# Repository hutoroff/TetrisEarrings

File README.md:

# ✨ TetrisEarrings

Earrings built on a 6×10 LED matrix with nine mesmerizing animated modes — from ping-pong and Tetris with an autonomous bot to fire, a starry sky, and rain on glass.

## About

A tiny STM32 board hidden inside the earring drives a matrix of 60 addressable RGB LEDs (6 columns × 10 rows). A single button switches modes manually, or they cycle on their own every 45 seconds. The device runs on a battery and can power itself off — either on a long button press or when the battery runs low — with a short farewell animation.

## Features

- 🎮 **9 modes** — from classic games to generative visual effects
- 🧠 **Tetris with a "smart" bot** — pieces don't just fall randomly: before each drop the bot tries every rotation and column and picks the placement using a heuristic (fewest holes, lowest height and bumpiness, most cleared lines)
- 🐍 **Snake with an autonomous bot** — finds its own path to the food and never runs into itself
- 🎨 **Sub-pixel smoothing** — the ping-pong balls move smoothly instead of jumping from LED to LED
- 🔋 **Smart power management** — continuous battery voltage monitoring and automatic shutdown on low battery
- 📺 **Power-off animation** — the screen "collapses" into a dot and fades out, like an old CRT TV
- 🧩 **Everything in 6 KB of RAM** — all modes share the same memory region (a union) instead of each mode keeping its own data

## Modes

| # | Mode | Description |
|---|---|---|
| 0 | Ping-Pong | Three balls fly around and bounce off each other, changing color on impact |
| 1 | Tetris | Autonomous game with a bot that deliberately chooses where to place each piece |
| 2 | Snake | Autonomous game; the bot steers the snake to the food by itself |
| 3 | Heart | A smoothly pulsing heart |
| 4 | Fire | Procedural simulation of a living flame with sparks |
| 5 | Matrix | Falling green "digital rain" in the style of *The Matrix* |
| 6 | Starry Sky | Sparse twinkling stars of different hues that slowly fade out |
| 7 | Rainbow | A shimmering diagonal rainbow wave |
| 8 | Rain on Glass | Drops trickle down and burst into splashes when they hit the bottom |

Short button press — next mode; hold for about a second — power off (with animation). With no presses, modes cycle automatically every 45 seconds.

## Hardware

| Parameter | Value |
|---|---|
| Microcontroller | STM32F070F6Px (Cortex-M0, 48 MHz, 32 KB Flash, 6 KB RAM) |
| Matrix | 6×10 (60 pcs) addressable RGB LEDs, WS2812-compatible protocol |
| Matrix data line | PA9 (TIM1_CH2 + DMA, per-bit PWM signal encoding) |
| Button | PA7 |
| Power control | PA6 (board power self-latch / shutdown) |
| Battery monitoring | PA1 (ADC1_IN1), auto-shutdown on low battery |
| Development environment | STM32CubeIDE 1.17.0, GNU Arm Embedded Toolchain 12.3.rel1 |

The matrix LEDs are wired in a "serpentine" layout: even rows run in one direction, odd rows in the other (see `GetLEDIndex()` in [ledMatrix.c](Core/Src/ledMatrix.c)).

### Power

1S Li-Po → P-MOSFET soft latch (button turns it on, PA6 holds it, PA6 low = off) → switched rail `VSW`. The LEDs run straight from `VSW` (3.5–4.2 V); the MCU gets 3.3 V from an LDO. Battery voltage is sensed on PA1 through a 62k/100k divider, so the firmware's 2700-count threshold means a **3.52 V** cutoff. Charging: MCP73831 at ~150 mA from two dock pads (the printed stand). Average draw ≈ 55–60 mA (mostly WS2812 idle current), so a 300 mAh 602030 cell gives ≈ 4.5 h.

### Components

| Qty | Ref | Part | Package | Note |
|---|---|---|---|---|
| 1 | U1 | STM32F070F6P6 | TSSOP-20 | MCU |
| 60 | LED1–LED60 | WS2812B-2020 | 2020 PLCC-4 | 6×10 matrix |
| 1 | U2 | MCP73831T-2ACI/OT | SOT-23-5 | Li-Po charger 4.2 V |
| 1 | U3 | ME6211C33M5G | SOT-23 | 3.3 V LDO |
| 1 | Q1 | AO3401A | SOT-23 | P-MOSFET power switch |
| 1 | Q2 | 2N7002 | SOT-23 | Latch driver |
| 2 | D1, D2 | BAT54W | SOD-323 | Latch OR diodes |
| 1 | D3 | LED red | 0603 | Charge indicator |
| 1 | Y1 | 8 MHz crystal | 3225 | HSE |
| 1 | SW1 | Tactile switch | SMD | Mode / power button |
| 1 | BT1 | Li-Po 1S 602030 300 mAh | 2 pads | With PCM; 602535 400 mAh for more runtime |
| — | J1 | TC2030-IDC-NL footprint | Tag-Connect pads | SWD; bare copper, nothing to buy |
| — | J2 | Dock contacts | 2 pads | 5 V charging; bare copper, nothing to buy |
| 5 | R1, R2, R3, R5, R8 | 100k | 0402 | Pull-ups/downs, dividers |
| 1 | R4 | 33k | 0402 | Button divider |
| 1 | R6 | 330 Ω | 0402 | LED data series |
| 1 | R7 | 62k | 0402 | Battery divider (cutoff) |
| 1 | R9 | 6.8k | 0402 | Charge current |
| 1 | R10 | 1k | 0402 | Charge LED |
| 1 | R11 | 10k | 0402 | BOOT0 |
| 13 | C5, C7, C8, C13–C22 | 100 nF | 0402 | Decoupling, NRST, LED rows |
| 3 | C3, C4, C6 | 1 µF | 0402 | LDO in/out, VDD |
| 2 | C9, C10 | 12 pF | 0402 | Crystal load |
| 1 | C11 | 10 nF | 0402 | ADC filter |
| 2 | C1, C2 | 4.7 µF | 0603 | Charger in/out |
| 1 | C12 | 10 µF | 0603 | LED rail bulk |

Total: 104 purchased components (24 BOM lines) plus 2 copper-pad footprints. Machine-readable list: [hardware/BOM.csv](hardware/BOM.csv).

## Electronics (Altium)

Schematic, PCB and BOM live in [`hardware/`](hardware/) as a KiCad project (text, generated by `gen_schematic.py` / `gen_pcb.py`). The PCB is 24 × 48 mm, 4 layers: the LEDs are on the front, everything else is on the back, and the inner layers are GND and VSW planes. It is fully routed, with DRC 0 errors and 0 differences from the schematic. Ready-to-upload JLCPCB files are in [`hardware/fab/`](hardware/fab/).

Altium Designer 21+ opens it directly: **File → Import Wizard → KiCad Design Files** → select the `hardware/` folder → Finish → **Project → Compile**. Circuit description, layout notes and tuning knobs (battery cutoff, charge current, battery size) are in [hardware/README.md](hardware/README.md).

## Building and Flashing

1. Clone the repository and open the project folder in **STM32CubeIDE 1.17.0** (File → Import → General → Existing Projects into Workspace).
2. Choose a build configuration:
   - **Debug** — full debug symbols, `-Og` optimization (chosen specifically so the firmware fits into the chip's 32 KB of flash while still being easy to debug);
   - **Release** — `-Os` build, minimal size.
3. **Project → Build Project**.
4. Flash via ST-Link: **Run → Debug** (or **Run**) with the programmer connected.

## Project Structure

```
Core/
├── Inc/                  # Headers
│   ├── effects.h          # Visual effects
│   ├── games.h            # Tetris and Snake
│   ├── ledMatrix.h        # WS2812 driver
│   └── saportAndData.h    # Shared state (pins, shared mode memory)
└── Src/
    ├── main.c              # Entry point, peripheral initialization
    ├── work.c               # Mode dispatcher, button, ADC, auto-shutdown
    ├── effects.c             # Ping-Pong, Fire, Matrix, Stars, Rainbow, Rain, Heart
    ├── games.c               # Tetris (with AI bot) and Snake (with autonomous bot)
    └── ledMatrix.c            # Addressable matrix driver on top of TIM1 + DMA
```

## License

This project is distributed under the [MIT](LICENSE) license.

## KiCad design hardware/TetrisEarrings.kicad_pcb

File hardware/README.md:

# TetrisEarrings — electronics

KiCad project generated by scripts; Altium Designer imports it natively.

| File | What |
|---|---|
| `TetrisEarrings.kicad_sch` / `.kicad_pro` | Schematic (single A2 sheet, all symbols embedded) |
| `TetrisEarrings.kicad_pcb` | PCB, 24 × 48 × 0.8 mm, 4 layers, fully routed |
| `TetrisEarrings.pretty/`, `fp-lib-table`, `sym-lib-table`, `.kicad_sym` | Project libraries (the two pad footprints; everything else is KiCad stock) |
| `BOM.csv` | Bill of materials, grouped by value/package |
| `fab/` | JLCPCB upload: Gerber+drill zip, BOM, CPL (pick-and-place) |
| `gen_schematic.py` | Schematic + BOM generator (Python 3, stdlib) |
| `gen_pcb.py` | Placement, fixed front copper, plane fanout (Python 3 + KiCad footprint libs) |
| `route.py` | Autorouting of the back-side signals with Freerouting (run with KiCad's Python) |
| `export_fab.py` | Gerbers, drill, BOM, CPL → `fab/` |

## Regenerate

```sh
python3 hardware/gen_schematic.py        # schematic + BOM
python3 hardware/gen_pcb.py              # board: placement, LED copper, fanout vias (unrouted signals)
/Applications/KiCad/KiCad.app/Contents/Frameworks/Python.framework/Versions/Current/bin/python3 hardware/route.py
python3 hardware/export_fab.py           # fab/ outputs
kicad-cli pcb drc --refill-zones --schematic-parity hardware/TetrisEarrings.kicad_pcb
```

`route.py` needs Java 17+ and `freerouting-1.9.0.jar` in `~/.cache/freerouting/fr-1.9.0.jar` (github.com/freerouting/freerouting/releases). A small Freerouting window appears while it routes. Freerouting 2.x ignores the pass limit in headless mode and never saves its result. Hand edits made in KiCad/Altium are lost on regeneration: either keep changing the scripts, or stop regenerating and treat the `.kicad_pcb` as the source from then on.

## Open in Altium Designer

1. **File → Import Wizard → KiCad Design Files** (Altium 21 or newer).
2. Add the `hardware/` folder (or the `.kicad_pro`), Next through the defaults, Finish.
3. Altium creates `TetrisEarrings.PrjPcb` with one `.SchDoc`. Run **Project → Compile** — it should report no errors; the sheet uses power ports and net labels on pin stubs, which the importer maps 1:1.
4. Optional: `kicad-cli sch export pdf TetrisEarrings.kicad_sch` for a PDF, or open in free KiCad.

## Circuit

**Power.** 1S Li-Po (602030, 300 mAh, with PCM) → `VBAT`. P-MOSFET Q1 (AO3401A) is the high-side switch producing the switched rail `VSW`, which feeds the LEDs directly (3.5–4.2 V, inside WS2812B-2020 spec) and the 3.3 V LDO U3 (ME6211) for the MCU.

**Soft latch** (matches `work.c`). Q1 gate is pulled to `VBAT` by R1 (off). Q2 (2N7002) pulls it low when `LATCH` is high; `LATCH` is the OR of the button (`KEY` via D1) and PA6 (`PWR_ON` via D2), R2 pull-down. Sequence: press → Q2 → Q1 → LDO → MCU boots, reads the button HIGH, sets PA6 = 1 → latch holds after release. PA6 = 0 (long press or low battery) → power drops; firmware spins in `while(1)` waiting for it.

**Button.** SW1 between `VBAT` and `KEY`, R3 100k pull-down (PA7 has no internal pull, pressed = HIGH). `KEY` → PA7 through R4 33k / R5 100k = 0.75·VBAT: 3.16 V at 4.2 V (≤ VDDA + 0.3), 2.6 V at 3.5 V (≥ 0.7·VDD).

**Battery sense.** R7 62k / R8 100k from `VSW` to PA1 (ADC_IN1), C11 filter. Firmware cutoff is 2700/4096 · 3.3 V = 2.175 V → **3.52 V** battery. On `VSW`, so no drain when off. Tune R7: 68k → 3.65 V, 56k → 3.39 V.

**Charger.** MCP73831-2 (4.2 V), input from two dock pads J2 (`VCHG` 5 V, GND — the printed stand acts as the dock), R9 6.8k → ~150 mA (0.5 C), D3 charge indicator. The charger connects straight to the battery, so charging works with the earring off.

**LEDs.** 60 × WS2812B-2020, DIN of LED1 from PA9 (TIM1_CH2) via R6 330 Ω. Chain order equals the firmware index from `GetLEDIndex()`: row 0 is the bottom row, even rows run right→left, odd rows left→right; LED*n* has index *n*−1. C12 10 µF bulk plus one 100 nF per row (C13–C22).

**MCU.** STM32F070F6P6 TSSOP-20, 8 MHz crystal Y1 with 12 pF loads (`ponytail:` set to the crystal's CL), BOOT0 10k to GND, NRST 100 nF, SWD via Tag-Connect TC2030 pads (J1). PA0, PA2–PA5, PA10, PB1 unused; PA3/PA4 (`Led1`/`Led2` in the `.ioc`) are initialised by firmware but never driven, so they are left unconnected.

## PCB layout

**Stackup** (JLC 4-layer, 0.8 mm):

| Layer | Contents |
|---|---|
| F.Cu | LEDs, data chain, power rails |
| In1 | GND plane |
| In2 | VSW plane |
| B.Cu | all other parts and signal routing |

The rules are the JLC standard: 0.15 mm track and clearance, 0.45/0.2 mm vias, 0.3 mm copper-to-edge.

**Front (jewellery face).**
- The LEDs sit on a 3.5 mm grid, and odd rows are rotated 180° so each DOUT→DIN hop is a short jog.
- Each gap between rows carries one power rail, alternating VSW and GND. Each rail hugs the row below it, which leaves a band where signal vias fit.
- The rails reach the planes only through vias in the board-edge strips (GND on the left, VSW on the right). This keeps the back free of a via grid.
- There is no silkscreen on the front, and there are 2 dock pads at the bottom edge.

**Back.**
- MCU in the middle, with the crystal right against PF0/PF1.
- Soft-latch parts near the top, and the button at the top edge so it stays accessible.
- Charger at the bottom, next to the Tag-Connect footprint (it has 3 NPTH alignment holes).
- Battery pads on the left edge. Glue the 602030 pouch over the back parts with kapton tape in between; the button and SWD pads stay uncovered.
- Every back-side GND/VSW pad has its own fanout via to its plane.
- 0.8 mm earring-hook hole at the top.

**Assembly.**
- JLC assembles both sides from `fab/`.
- BT1 is excluded from the CPL; solder the pouch tabs by hand.
- J1/J2 are bare copper.
- JLC's CPL preview sometimes shows parts rotated (a known library-orientation quirk, typically on SOT-23 and TSSOP). Check the rotation preview on the order page before paying.

## Power budget / battery choice

WS2812B-2020 idle current ≈ 0.6–0.7 mA each → ~40 mA for 60 LEDs, MCU ≈ 8 mA, lit-LED average ≈ 8 mA (effects stay ≤ ~25 % per channel) → **≈ 55–60 mA**. 300 mAh usable to 3.5 V ≈ 4.5 h. For more margin use 602535 (400 mAh, ≈ 6 h) — same pads, BOM change only.

Footprints `TetrisEarrings:Pad_Battery_2x` and `Pad_Dock_2x` are placeholders for two solder pads each; draw them to the pad/contact geometry of your dock.

## Verification (KiCad 10.0.6)

- `kicad-cli sch erc`: 0 errors, 0 warnings.
- `kicad-cli pcb drc --refill-zones --schematic-parity`: 0 errors, 0 unconnected items, 0 schematic-parity issues.
- The only warnings are 61 "footprint differs from library":
  - 60 are the LEDs, whose front silkscreen was removed on purpose.
  - 1 is the Tag-Connect footprint mirrored to the back.
- `TetrisEarrings.pdf` is the rendered schematic.

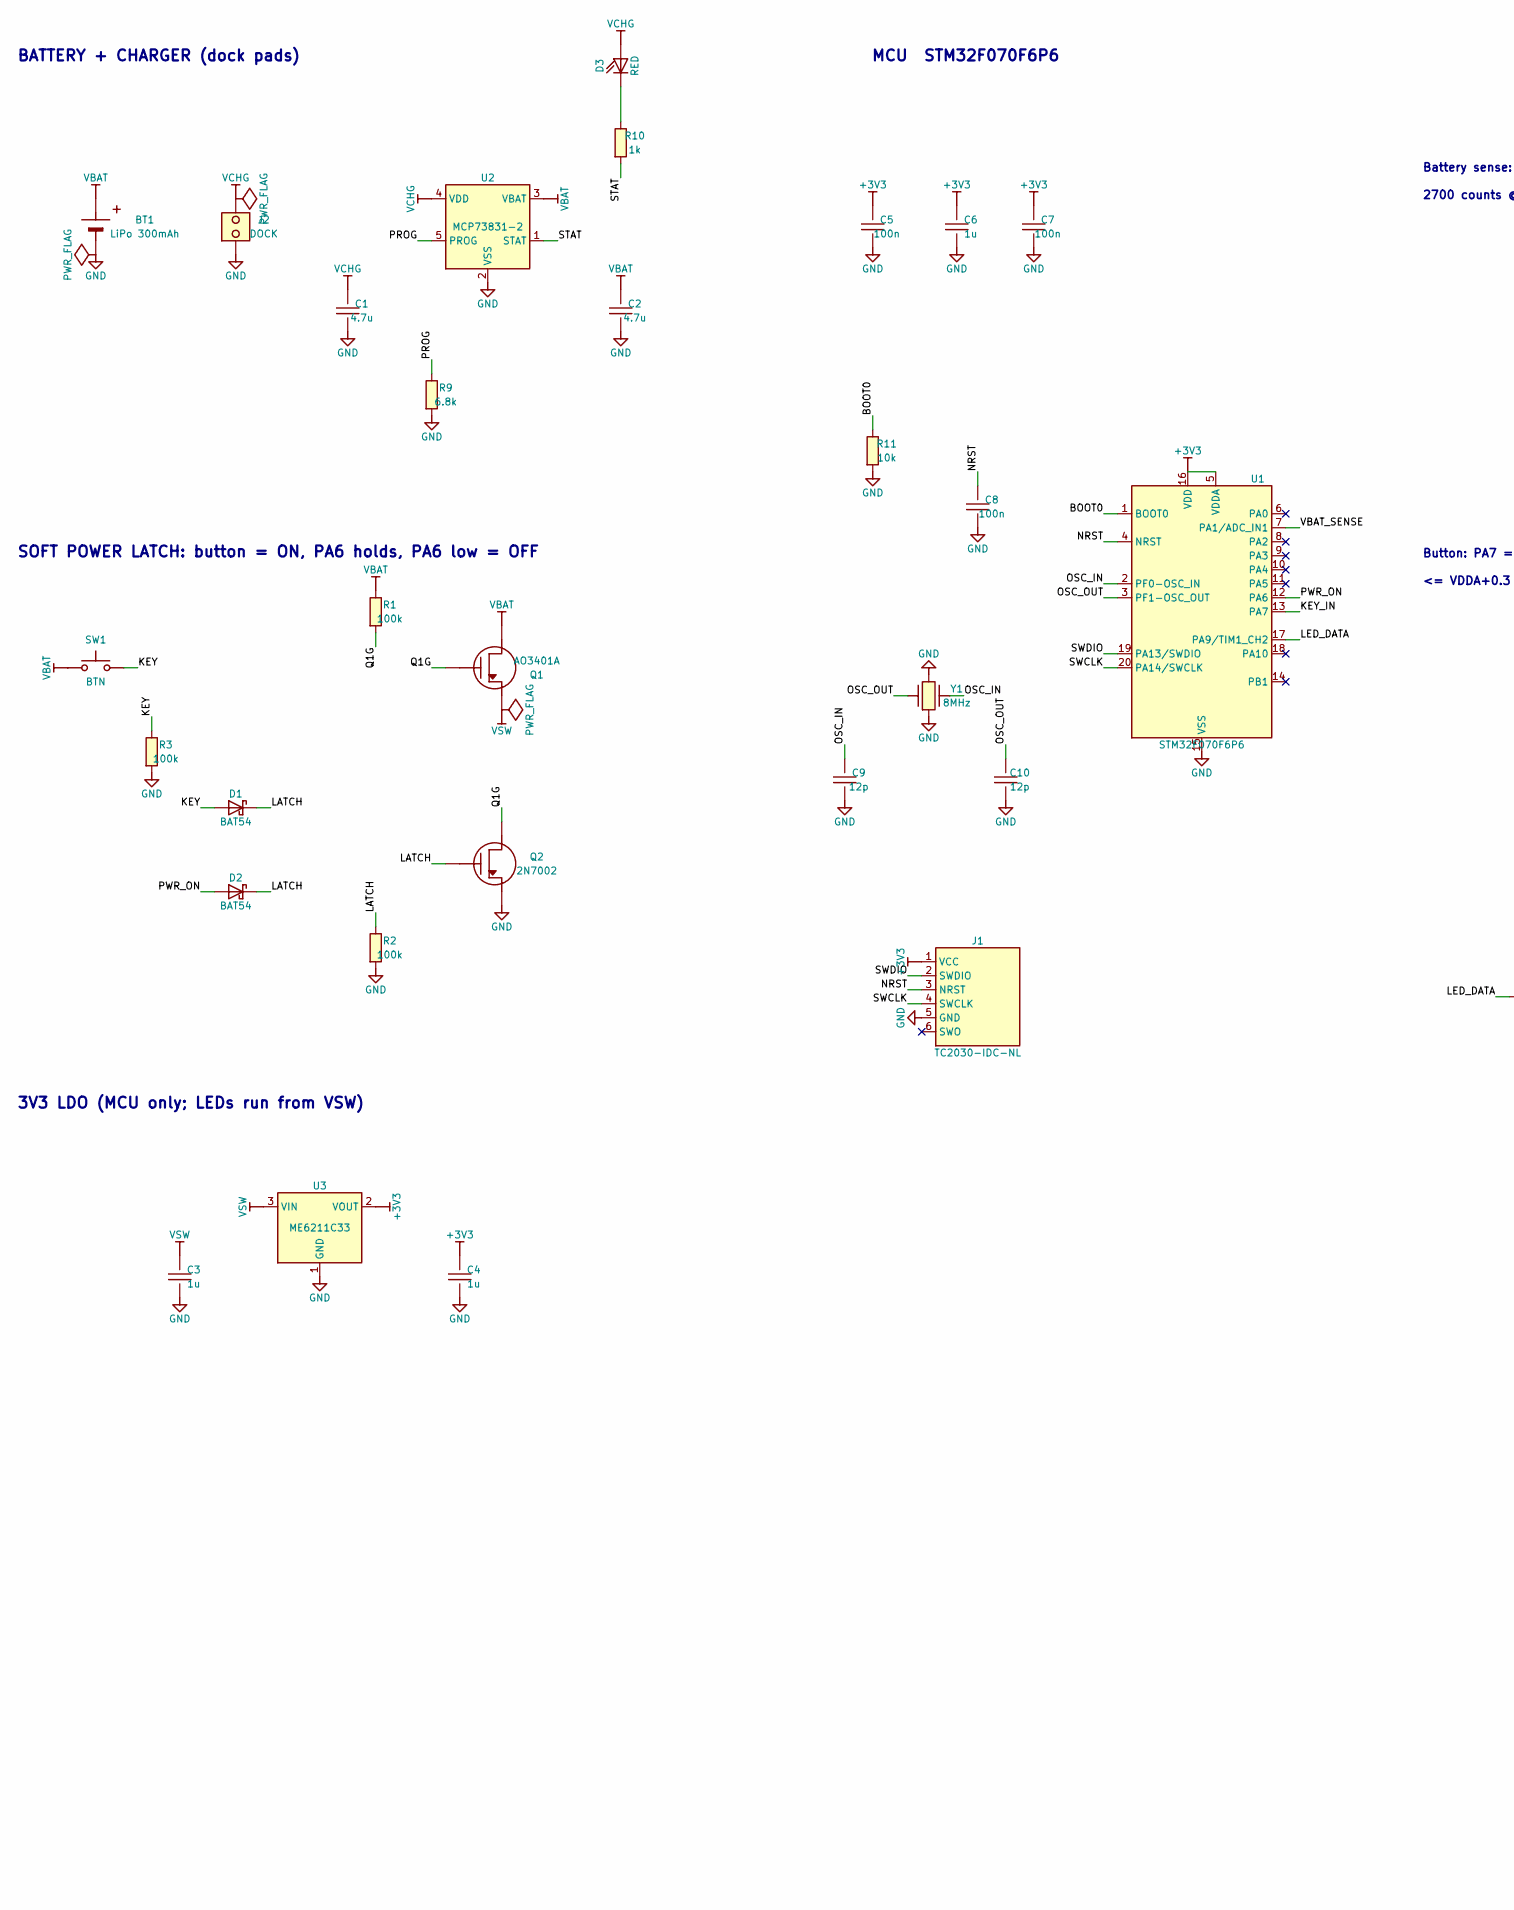
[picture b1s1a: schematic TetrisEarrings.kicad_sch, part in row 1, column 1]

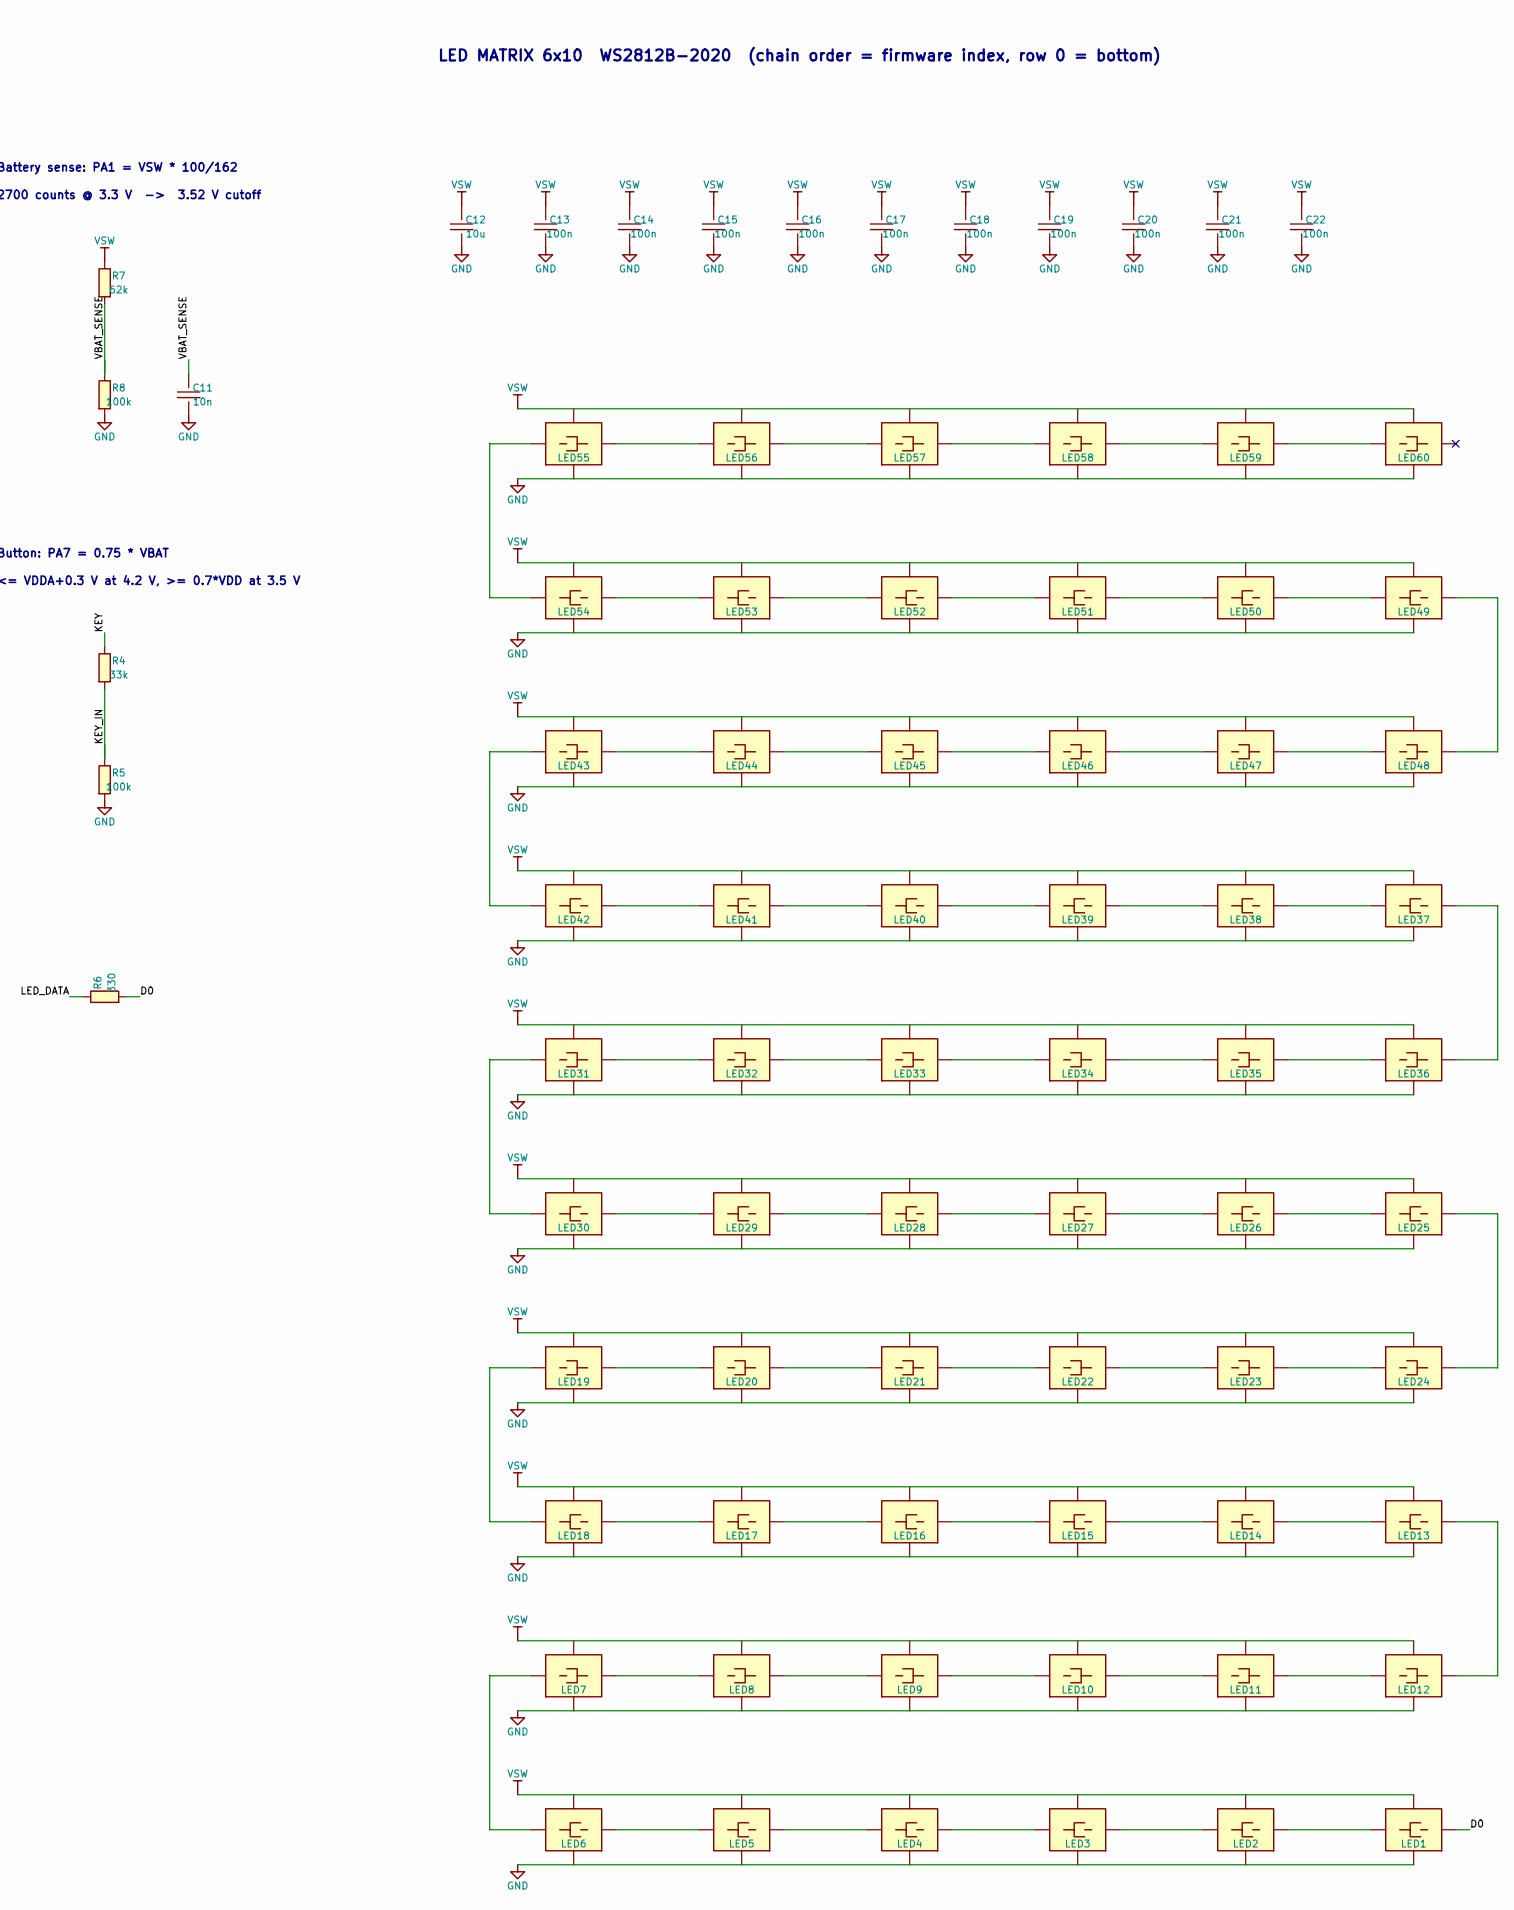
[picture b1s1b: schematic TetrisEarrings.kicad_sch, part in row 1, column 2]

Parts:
BT1: LiPo 300mAh; Pad_Battery_2x
C1, C2: 4.7u; C_0603_1608Metric
C3, C4, C6: 1u; C_0402_1005Metric
C5, C7, C8, C13, C14, C15, C16, C17, C18, C19, C20, C21, C22: 100n; C_0402_1005Metric
C9, C10: 12p; C_0402_1005Metric
C11: 10n; C_0402_1005Metric
C12: 10u; C_0603_1608Metric
D1, D2: BAT54; D_SOD-323; MPN BAT54W
D3: RED; LED_0603_1608Metric
J1: TC2030-IDC-NL; Tag-Connect_TC2030-IDC-NL_2x03_P1.27mm_Vertical
J2: DOCK; Pad_Dock_2x
LED1, LED2, LED3, LED4, LED5, LED6, LED7, LED8, LED9, LED10, LED11, LED12, LED13, LED14, LED15, LED16, LED17, LED18, LED19, LED20, LED21, LED22, LED23, LED24, LED25, LED26, LED27, LED28, LED29, LED30, LED31, LED32, LED33, LED34, LED35, LED36, LED37, LED38, LED39, LED40, LED41, LED42, LED43, LED44, LED45, LED46, LED47, LED48, LED49, LED50, LED51, LED52, LED53, LED54, LED55, LED56, LED57, LED58, LED59, LED60: WS2812B-2020; LED_WS2812B-2020_PLCC4_2.0x2.0mm; MPN WS2812B-2020
Q1: AO3401A; SOT-23; MPN AO3401A
Q2: 2N7002; SOT-23; MPN 2N7002
R1, R2, R3, R5, R8: 100k; R_0402_1005Metric
R4: 33k; R_0402_1005Metric
R6: 330; R_0402_1005Metric
R7: 62k; R_0402_1005Metric
R9: 6.8k; R_0402_1005Metric
R10: 1k; R_0402_1005Metric
R11: 10k; R_0402_1005Metric
SW1: BTN; SW_Push_1P1T_NO_CK_KMR2
U1: STM32F070F6P6; TSSOP-20_4.4x6.5mm_P0.65mm; MPN STM32F070F6P6
U2: MCP73831-2; SOT-23-5; MPN MCP73831T-2ACI/OT
U3: ME6211C33; SOT-23; MPN ME6211C33M5G-N
Y1: 8MHz; Crystal_SMD_3225-4Pin_3.2x2.5mm

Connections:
+3V3: C4.1, C5.1, C6.1, C7.1, J1.1 (VCC), U1.5 (VDDA), U1.16 (VDD), U3.2 (VOUT)
/BOOT0: R11.1, U1.1 (BOOT0)
/D0: LED1.4 (DIN), R6.2
/KEY: D1.2 (A), R3.1, R4.1, SW1.2
/KEY_IN: R4.2, R5.1, U1.13 (PA7)
/LATCH: D1.1 (K), D2.1 (K), Q2.1 (G), R2.1
/LED_DATA: R6.1, U1.17 (PA9/TIM1_CH2)
/NRST: C8.1, J1.3 (NRST), U1.4 (NRST)
/OSC_IN: C9.1, U1.2 (PF0-OSC_IN), Y1.3
/OSC_OUT: C10.1, U1.3 (PF1-OSC_OUT), Y1.1
/PROG: R9.1, U2.5 (PROG)
/PWR_ON: D2.2 (A), U1.12 (PA6)
/Q1G: Q1.1 (G), Q2.3 (D), R1.2
/STAT: R10.2, U2.1 (STAT)
/SWCLK: J1.4 (SWCLK), U1.20 (PA14/SWCLK)
/SWDIO: J1.2 (SWDIO), U1.19 (PA13/SWDIO)
/VBAT_SENSE: C11.1, R7.2, R8.1, U1.7 (PA1/ADC_IN1)
GND: BT1.2 (-), C1.2, C2.2, C3.2, C4.2, C5.2, C6.2, C7.2, C8.2, C9.2, C10.2, C11.2, C12.2, C13.2, C14.2, C15.2, C16.2, C17.2, C18.2, C19.2, C20.2, C21.2, C22.2, J1.5 (GND), J2.2, LED1.3 (GND), LED2.3 (GND), LED3.3 (GND), LED4.3 (GND), LED5.3 (GND), LED6.3 (GND), LED7.3 (GND), LED8.3 (GND), LED9.3 (GND), LED10.3 (GND), LED11.3 (GND), LED12.3 (GND), LED13.3 (GND), LED14.3 (GND), LED15.3 (GND), LED16.3 (GND), LED17.3 (GND), LED18.3 (GND), LED19.3 (GND), LED20.3 (GND), LED21.3 (GND), LED22.3 (GND), LED23.3 (GND), LED24.3 (GND), LED25.3 (GND), LED26.3 (GND), LED27.3 (GND), LED28.3 (GND), LED29.3 (GND), LED30.3 (GND), LED31.3 (GND), LED32.3 (GND), LED33.3 (GND), LED34.3 (GND), LED35.3 (GND), LED36.3 (GND), LED37.3 (GND), LED38.3 (GND), LED39.3 (GND), LED40.3 (GND), LED41.3 (GND), LED42.3 (GND), LED43.3 (GND), LED44.3 (GND), LED45.3 (GND), LED46.3 (GND), LED47.3 (GND), LED48.3 (GND), LED49.3 (GND), LED50.3 (GND), LED51.3 (GND), LED52.3 (GND), LED53.3 (GND), LED54.3 (GND), LED55.3 (GND), LED56.3 (GND), LED57.3 (GND), LED58.3 (GND), LED59.3 (GND), LED60.3 (GND), Q2.2 (S), R2.2, R3.2, R5.2, R8.2, R9.2, R11.2, U1.15 (VSS), U2.2 (VSS), U3.1 (GND), Y1.2 (GND), Y1.4 (GND)
unnamed: D3.1 (K), R10.1
unnamed: LED1.2 (DOUT), LED2.4 (DIN)
unnamed: LED2.2 (DOUT), LED3.4 (DIN)
unnamed: LED3.2 (DOUT), LED4.4 (DIN)
unnamed: LED4.2 (DOUT), LED5.4 (DIN)
unnamed: LED5.2 (DOUT), LED6.4 (DIN)
unnamed: LED6.2 (DOUT), LED7.4 (DIN)
unnamed: LED7.2 (DOUT), LED8.4 (DIN)
unnamed: LED8.2 (DOUT), LED9.4 (DIN)
unnamed: LED9.2 (DOUT), LED10.4 (DIN)
unnamed: LED10.2 (DOUT), LED11.4 (DIN)
unnamed: LED11.2 (DOUT), LED12.4 (DIN)
unnamed: LED12.2 (DOUT), LED13.4 (DIN)
unnamed: LED13.2 (DOUT), LED14.4 (DIN)
unnamed: LED14.2 (DOUT), LED15.4 (DIN)
unnamed: LED15.2 (DOUT), LED16.4 (DIN)
unnamed: LED16.2 (DOUT), LED17.4 (DIN)
unnamed: LED17.2 (DOUT), LED18.4 (DIN)
unnamed: LED18.2 (DOUT), LED19.4 (DIN)
unnamed: LED19.2 (DOUT), LED20.4 (DIN)
unnamed: LED20.2 (DOUT), LED21.4 (DIN)
unnamed: LED21.2 (DOUT), LED22.4 (DIN)
unnamed: LED22.2 (DOUT), LED23.4 (DIN)
unnamed: LED23.2 (DOUT), LED24.4 (DIN)
unnamed: LED24.2 (DOUT), LED25.4 (DIN)
unnamed: LED25.2 (DOUT), LED26.4 (DIN)
unnamed: LED26.2 (DOUT), LED27.4 (DIN)
unnamed: LED27.2 (DOUT), LED28.4 (DIN)
unnamed: LED28.2 (DOUT), LED29.4 (DIN)
unnamed: LED29.2 (DOUT), LED30.4 (DIN)
unnamed: LED30.2 (DOUT), LED31.4 (DIN)
unnamed: LED31.2 (DOUT), LED32.4 (DIN)
unnamed: LED32.2 (DOUT), LED33.4 (DIN)
unnamed: LED33.2 (DOUT), LED34.4 (DIN)
unnamed: LED34.2 (DOUT), LED35.4 (DIN)
unnamed: LED35.2 (DOUT), LED36.4 (DIN)
unnamed: LED36.2 (DOUT), LED37.4 (DIN)
unnamed: LED37.2 (DOUT), LED38.4 (DIN)
unnamed: LED38.2 (DOUT), LED39.4 (DIN)
unnamed: LED39.2 (DOUT), LED40.4 (DIN)
unnamed: LED40.2 (DOUT), LED41.4 (DIN)
unnamed: LED41.2 (DOUT), LED42.4 (DIN)
unnamed: LED42.2 (DOUT), LED43.4 (DIN)
unnamed: LED43.2 (DOUT), LED44.4 (DIN)
unnamed: LED44.2 (DOUT), LED45.4 (DIN)
unnamed: LED45.2 (DOUT), LED46.4 (DIN)
unnamed: LED46.2 (DOUT), LED47.4 (DIN)
unnamed: LED47.2 (DOUT), LED48.4 (DIN)
unnamed: LED48.2 (DOUT), LED49.4 (DIN)
unnamed: LED49.2 (DOUT), LED50.4 (DIN)
unnamed: LED50.2 (DOUT), LED51.4 (DIN)
unnamed: LED51.2 (DOUT), LED52.4 (DIN)
unnamed: LED52.2 (DOUT), LED53.4 (DIN)
unnamed: LED53.2 (DOUT), LED54.4 (DIN)
unnamed: LED54.2 (DOUT), LED55.4 (DIN)
unnamed: LED55.2 (DOUT), LED56.4 (DIN)
unnamed: LED56.2 (DOUT), LED57.4 (DIN)
unnamed: LED57.2 (DOUT), LED58.4 (DIN)
unnamed: LED58.2 (DOUT), LED59.4 (DIN)
unnamed: LED59.2 (DOUT), LED60.4 (DIN)
VBAT: BT1.1 (+), C2.1, Q1.2 (S), R1.1, SW1.1, U2.3 (VBAT)
VCHG: C1.1, D3.2 (A), J2.1, U2.4 (VDD)
VSW: C3.1, C12.1, C13.1, C14.1, C15.1, C16.1, C17.1, C18.1, C19.1, C20.1, C21.1, C22.1, LED1.1 (VDD), LED2.1 (VDD), LED3.1 (VDD), LED4.1 (VDD), LED5.1 (VDD), LED6.1 (VDD), LED7.1 (VDD), LED8.1 (VDD), LED9.1 (VDD), LED10.1 (VDD), LED11.1 (VDD), LED12.1 (VDD), LED13.1 (VDD), LED14.1 (VDD), LED15.1 (VDD), LED16.1 (VDD), LED17.1 (VDD), LED18.1 (VDD), LED19.1 (VDD), LED20.1 (VDD), LED21.1 (VDD), LED22.1 (VDD), LED23.1 (VDD), LED24.1 (VDD), LED25.1 (VDD), LED26.1 (VDD), LED27.1 (VDD), LED28.1 (VDD), LED29.1 (VDD), LED30.1 (VDD), LED31.1 (VDD), LED32.1 (VDD), LED33.1 (VDD), LED34.1 (VDD), LED35.1 (VDD), LED36.1 (VDD), LED37.1 (VDD), LED38.1 (VDD), LED39.1 (VDD), LED40.1 (VDD), LED41.1 (VDD), LED42.1 (VDD), LED43.1 (VDD), LED44.1 (VDD), LED45.1 (VDD), LED46.1 (VDD), LED47.1 (VDD), LED48.1 (VDD), LED49.1 (VDD), LED50.1 (VDD), LED51.1 (VDD), LED52.1 (VDD), LED53.1 (VDD), LED54.1 (VDD), LED55.1 (VDD), LED56.1 (VDD), LED57.1 (VDD), LED58.1 (VDD), LED59.1 (VDD), LED60.1 (VDD), Q1.3 (D), R7.1, U3.3 (VIN)

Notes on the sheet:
BATTERY + CHARGER (dock pads)
SOFT POWER LATCH: button = ON, PA6 holds, PA6 low = OFF
3V3 LDO (MCU only; LEDs run from VSW)
MCU STM32F070F6P6
Battery sense: PA1 = VSW * 100/162
2700 counts @ 3.3 V -> 3.52 V cutoff
Button: PA7 = 0.75 * VBAT
<= VDDA+0.3 V at 4.2 V, >= 0.7*VDD at 3.5 V
LED MATRIX 6x10 WS2812B-2020 (chain order = firmware index, row 0 = bottom)

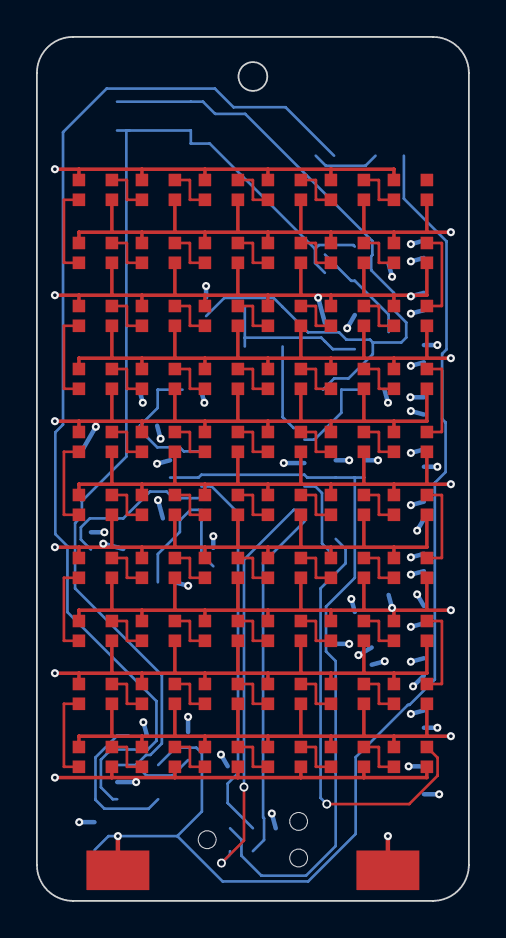
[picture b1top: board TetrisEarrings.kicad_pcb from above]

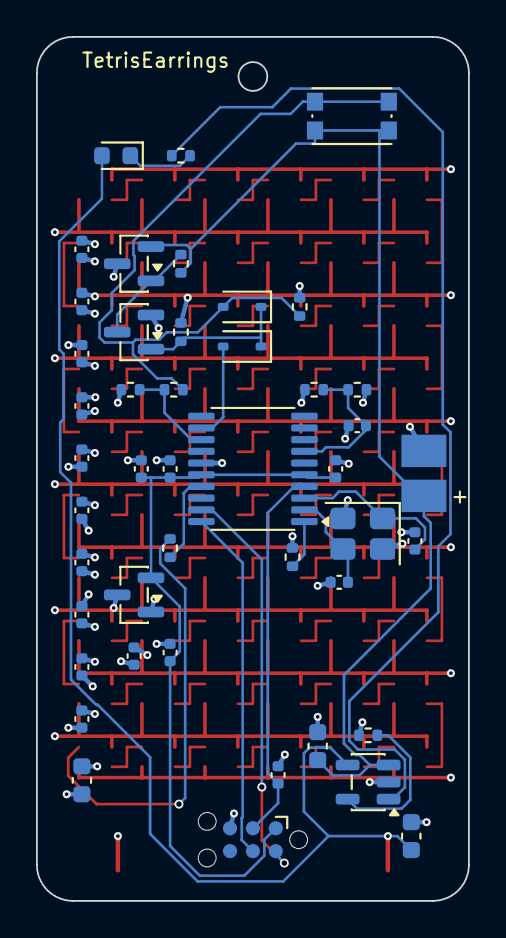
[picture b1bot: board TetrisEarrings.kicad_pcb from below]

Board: 4 copper layers, 24.0 x 48.0 mm, 106 parts (45 on the bottom side), 81 nets.

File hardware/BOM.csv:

Refs,Qty,Value,Package,MPN,Description
BT1,1,LiPo 300mAh,Pad_Battery_2x,,"1S Li-Po 602030 (6x20x30 mm) with PCM, solder pads"
"C1, C2",2,4.7u,C_0603_1608Metric,,Charger input; Charger output / battery
"C3, C4, C6",3,1u,C_0402_1005Metric,,LDO input; LDO output; VDD bulk
"C5, C7, C8, C13, C14, C15, C16, C17, C18, C19, C20, C21, C22",13,100n,C_0402_1005Metric,,VDD decoupling; VDDA decoupling; NRST filter; LED row decoupling
"C9, C10",2,12p,C_0402_1005Metric,,Crystal load
C11,1,10n,C_0402_1005Metric,,ADC filter
C12,1,10u,C_0603_1608Metric,,LED rail bulk
"D1, D2",2,BAT54,D_SOD-323,BAT54W,Button -> latch OR; PA6 -> latch OR
D3,1,RED,LED_0603_1608Metric,,Charging indicator
LED1-LED60,60,WS2812B-2020,LED_WS2812B-2020_PLCC4_2.0x2.0mm,WS2812B-2020,Addressable RGB LED 2x2 mm
Q1,1,AO3401A,SOT-23,AO3401A,High-side P-MOSFET switch
Q2,1,2N7002,SOT-23,2N7002,Latch driver
"R1, R2, R3, R5, R8",5,100k,R_0402_1005Metric,,Q1 gate pull-up (off); Latch pull-down; Button pull-down; Battery divider bottom; Button divider bottom
R4,1,33k,R_0402_1005Metric,,Button divider top
R6,1,330,R_0402_1005Metric,,LED data series
R7,1,62k,R_0402_1005Metric,,Battery divider top (sets 3.52 V cutoff)
R9,1,6.8k,R_0402_1005Metric,,Charge current 1000V/R = 147 mA
R10,1,1k,R_0402_1005Metric,,Charge LED series
R11,1,10k,R_0402_1005Metric,,BOOT0 pull-down
SW1,1,BTN,SW_Push_1P1T_NO_CK_KMR2,,Tactile button (mode / power)
U1,1,STM32F070F6P6,TSSOP-20_4.4x6.5mm_P0.65mm,STM32F070F6P6,"Cortex-M0 MCU, TSSOP-20"
U2,1,MCP73831-2,SOT-23-5,MCP73831T-2ACI/OT,"Li-Po charger 4.2 V, ~150 mA"
U3,1,ME6211C33,SOT-23,ME6211C33M5G-N,"3.3 V LDO, low dropout"
Y1,1,8MHz,Crystal_SMD_3225-4Pin_3.2x2.5mm,,"HSE 8 MHz, 3225"

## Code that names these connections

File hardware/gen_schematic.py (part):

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
defsym("MCP73831", "U", [rect(-7.62, -7.62, 7.62, 7.62)],
       [pin("4", "VDD", "power_in", -10.16, 5.08, 0),
        pin("5", "PROG", "input", -10.16, -2.54, 0),
        pin("3", "VBAT", "power_out", 10.16, 5.08, 180),
        pin("1", "STAT", "open_collector", 10.16, -2.54, 180),
        pin("2", "VSS", "power_in", 0, -10.16, 90)],
       ref_at=(0, 8.89), val_at=(0, 0))

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        pin("15", "VSS", "power_in", 0, -25.4, 90),
        pin("1", "BOOT0", "input", -15.24, 17.78, 0),
        pin("4", "NRST", "input", -15.24, 12.7, 0),
        pin("2", "PF0-OSC_IN", "bidirectional", -15.24, 5.08, 0),
        pin("3", "PF1-OSC_OUT", "bidirectional", -15.24, 2.54, 0),
        pin("19", "PA13/SWDIO", "bidirectional", -15.24, -7.62, 0),
        pin("20", "PA14/SWCLK", "bidirectional", -15.24, -10.16, 0),
        pin("6", "PA0", "bidirectional", 15.24, 17.78, 180),
        pin("7", "PA1/ADC_IN1", "bidirectional", 15.24, 15.24, 180),
        pin("8", "PA2", "bidirectional", 15.24, 12.7, 180),
        pin("9", "PA3", "bidirectional", 15.24, 10.16, 180),
        pin("10", "PA4", "bidirectional", 15.24, 7.62, 180),
        pin("11", "PA5", "bidirectional", 15.24, 5.08, 180),
        pin("12", "PA6", "bidirectional", 15.24, 2.54, 180),
        pin("13", "PA7", "bidirectional", 15.24, 0, 180),
        pin("17", "PA9/TIM1_CH2", "bidirectional", 15.24, -5.08, 180),
        pin("18", "PA10", "bidirectional", 15.24, -7.62, 180),
        pin("14", "PB1", "bidirectional", 15.24, -12.7, 180)],
       ref_at=(10.16, 24.13), val_at=(0, -24.13))
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sh.connect("D3", "1", "R10", "1")

# --- soft power latch ----------------------------------------------------
sh.text("SOFT POWER LATCH: button = ON, PA6 holds, PA6 low = OFF", 25, 120)
sh.part("Q1", "Q_PMOS_GSD", 110, 140, 0, "AO3401A", SOT23,
        {"1": "Q1G", "2": "VBAT", "3": "VSW"}, mpn="AO3401A", desc="High-side P-MOSFET switch", mirror="x")
sh.pwr_flag("Q1", "3", side=(1, 0))   # VSW is sourced by Q1 drain (passive)
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sh.part("D1", "D_Schottky", 65, 165, 0, "BAT54", SOD323, {"1": "LATCH", "2": "KEY"},
        mpn="BAT54W", desc="Button -> latch OR", mirror="y")
sh.part("D2", "D_Schottky", 65, 180, 0, "BAT54", SOD323, {"1": "LATCH", "2": "PWR_ON"},
        mpn="BAT54W", desc="PA6 -> latch OR", mirror="y")
sh.part("SW1", "SW_Push", 40, 140, 0, "BTN", "Button_Switch_SMD:SW_Push_1P1T_NO_CK_KMR2",
        {"1": "VBAT", "2": "KEY"}, desc="Tactile button (mode / power)")
sh.part("R3", "R", 50, 155, 0, "100k", R0402, {"1": "KEY", "2": "GND"}, desc="Button pull-down")
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        {"1": "+3V3", "2": "SWDIO", "3": "NRST", "4": "SWCLK", "5": "GND", "6": None},
        desc="SWD programming pads (Tag-Connect footprint, no header)")

sh.text("Battery sense: PA1 = VSW * 100/162", 280, 50, 1.5)
sh.text("2700 counts @ 3.3 V  ->  3.52 V cutoff", 280, 55, 1.5)
sh.part("R7", "R", 300, 70, 0, "62k", R0402, {"1": "VSW", "2": "!"}, desc="Battery divider top (sets 3.52 V cutoff)")
sh.part("R8", "R", 300, 90, 0, "100k", R0402, {"1": "VBAT_SENSE", "2": "GND"}, desc="Battery divider bottom")
sh.connect("R7", "2", "R8", "1")
sh.part("C11", "C", 315, 90, 0, "10n", C0402, {"1": "VBAT_SENSE", "2": "GND"}, desc="ADC filter")
sh.text("Button: PA7 = 0.75 * VBAT", 280, 120, 1.5)
sh.text("<= VDDA+0.3 V at 4.2 V, >= 0.7*VDD at 3.5 V", 280, 125, 1.5)
sh.part("R4", "R", 300, 140, 0, "33k", R0402, {"1": "KEY", "2": "!"}, desc="Button divider top")
sh.part("R5", "R", 300, 160, 0, "100k", R0402, {"1": "KEY_IN", "2": "GND"}, desc="Button divider bottom")
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                mirror="" if y % 2 else "y", show_value=False)   # even rows flow right->left
    first = f"LED{y * 6 + 1}"
    row = [f"LED{y * 6 + 1 + i}" for i in range(6)]
    sh.rail("VSW", [sh.pin_at(r, "1") for r in row], (X0 - 10.16, sh.pin_at(first, "1")[1]))
    sh.rail("GND", [sh.pin_at(r, "3") for r in row], (X0 - 10.16, sh.pin_at(first, "3")[1]))
    # one 100 nF per row, on the row's rails
    sh.part(f"C{13 + y}", "C", 380 + y * 15.24, 60, 0, "100n", C0402, {"1": "VSW", "2": "GND"},
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

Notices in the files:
README.md:
License: MIT
